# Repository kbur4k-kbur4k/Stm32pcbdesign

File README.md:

# STM32F103 DEV KIT Printed Circuit Board Design

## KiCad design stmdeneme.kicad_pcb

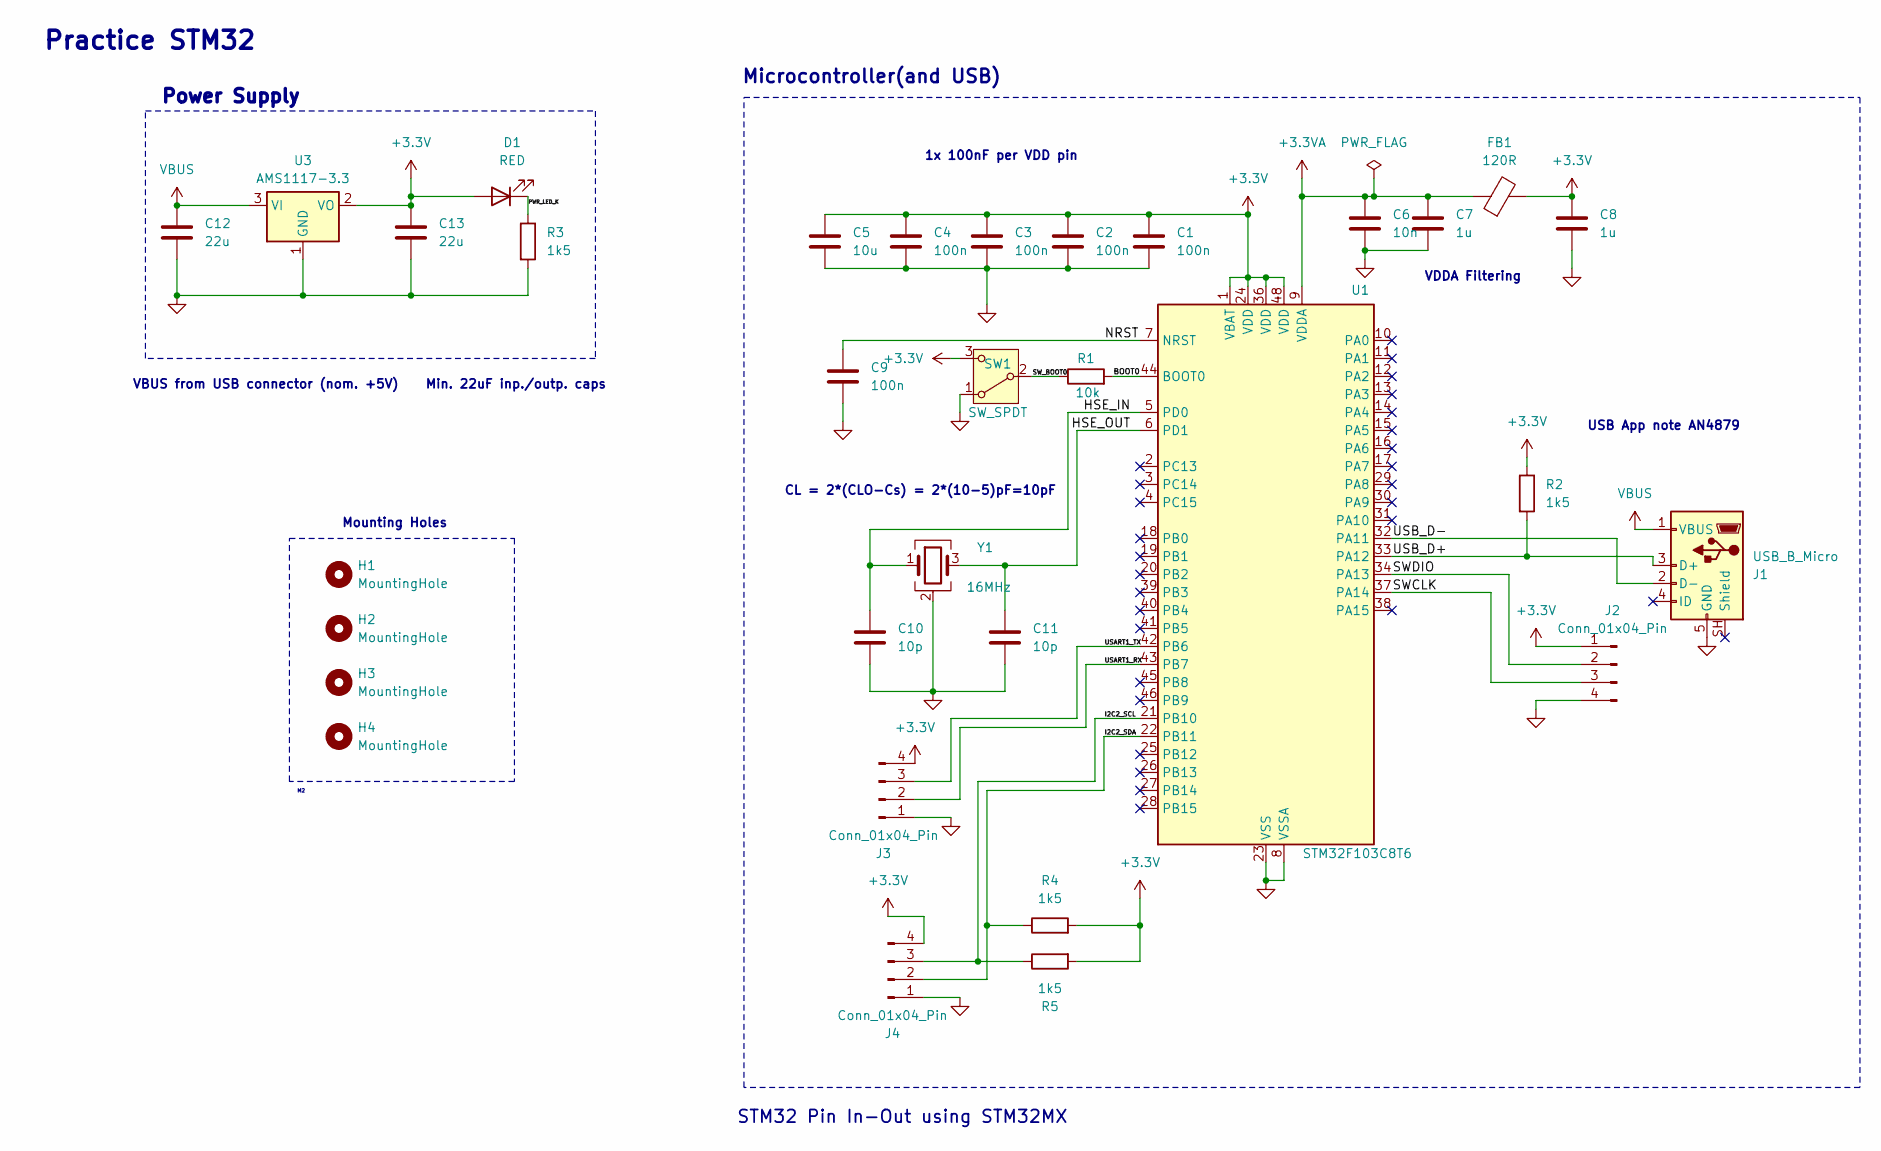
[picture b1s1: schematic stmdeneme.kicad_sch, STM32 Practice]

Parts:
C1, C2, C3, C4, C9: 100n; C_0402_1005Metric
C5: 10u; C_0603_1608Metric
C6: 10n; C_0402_1005Metric
C7, C8: 1u; C_0402_1005Metric
C10, C11: 10p; C_0402_1005Metric
C12, C13: 22u; C_0805_2012Metric
D1: RED; LED_0603_1608Metric
FB1: 120R; L_0603_1608Metric
H1, H2, H3, H4: MountingHole; MountingHole_2.1mm
J1: USB_B_Micro; USB_Micro-B_Wuerth_629105150521
J2, J3, J4: Conn_01x04_Pin; PinHeader_1x04_P2.54mm_Vertical
R1: 10k; R_0402_1005Metric
R2, R3, R4, R5: 1k5; R_0402_1005Metric
SW1: SW_SPDT; SW_SPDT_PCM12
U1: STM32F103C8T6; LQFP-48_7x7mm_P0.5mm
U3: AMS1117-3.3; SOT-223-3_TabPin2
Y1: 16MHz; Crystal_SMD_3225-4Pin_3.2x2.5mm

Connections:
+3.3V: C1.1, C2.1, C3.1, C4.1, C5.1, C8.1, C13.1, D1.2 (A), FB1.2, J2.1, J3.4, J4.4, R2.1, R4.2, R5.2, SW1.3 (C), U1.1 (VBAT), U1.24 (VDD), U1.36 (VDD), U1.48 (VDD), U3.2 (VO)
+3.3VA: C6.1, C7.1, FB1.1, U1.9 (VDDA)
/BOOT0: R1.2, U1.44 (BOOT0)
/HSE_IN: C10.1, U1.5 (PD0), Y1.1
/HSE_OUT: C11.1, U1.6 (PD1), Y1.3
/I2C2_SCL: J4.3, R5.1, U1.21 (PB10)
/I2C2_SDA: J4.2, R4.1, U1.22 (PB11)
/NRST: C9.1, U1.7 (NRST)
/PWR_LED_K: D1.1 (K), R3.1
/SWCLK: J2.3, U1.37 (PA14)
/SWDIO: J2.2, U1.34 (PA13)
/SW_BOOT0: R1.1, SW1.2 (B)
/USART1_RX: J3.2, U1.43 (PB7)
/USART1_TX: J3.3, U1.42 (PB6)
/USB_D+: J1.3 (D+), R2.2, U1.33 (PA12)
/USB_D-: J1.2 (D-), U1.32 (PA11)
GND: C1.2, C2.2, C3.2, C4.2, C5.2, C6.2, C7.2, C8.2, C9.2, C10.2, C11.2, C12.2, C13.2, J1.5 (GND), J2.4, J3.1, J4.1, R3.2, SW1.1 (A), U1.8 (VSSA), U1.23 (VSS), U1.35 (VSS), U1.47 (VSS), U3.1 (GND), Y1.2 (G), Y1.4 (G)
VBUS: C12.1, J1.1 (VBUS), U3.3 (VI)

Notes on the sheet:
Practice STM32
VDDA Filtering
1x 100nF per VDD pin
Power Supply
STM32 Pin In-Out using STM32MX
USB App note AN4879
CL = 2*(CLO-Cs) = 2*(10-5)pF=10pF
Microcontroller(and USB)
Mounting Holes
VBUS from USB connector (nom. +5V) Min. 22uF inp./outp. caps

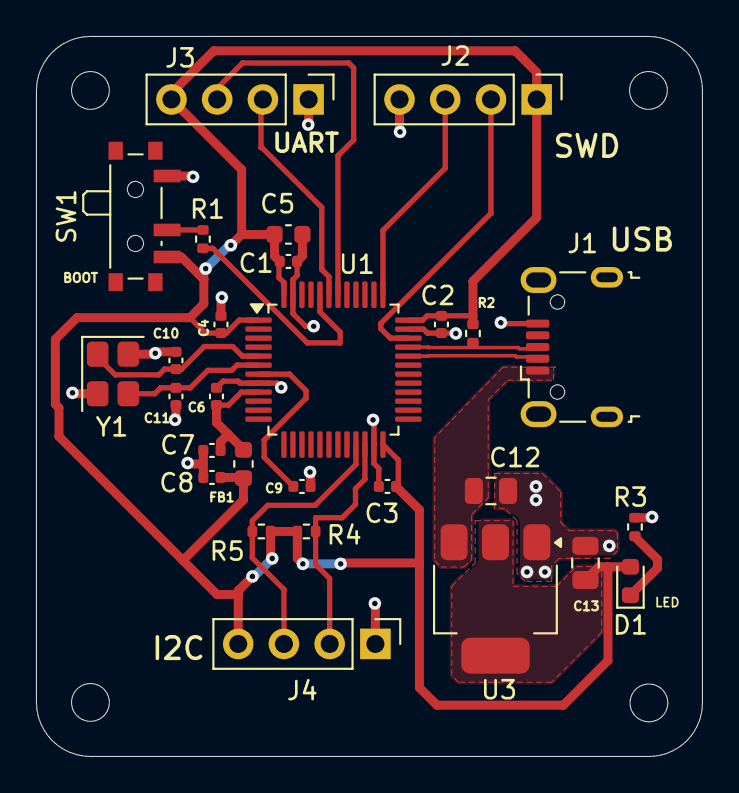
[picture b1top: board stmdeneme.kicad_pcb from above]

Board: 2 copper layers, 37.0 x 40.0 mm, 32 parts (0 on the bottom side), 18 nets.
